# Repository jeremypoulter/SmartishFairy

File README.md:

# SmartishFairy

## Overview
SmartishFairy is a smart controller for inexpensive consumer fairy lights that provides advanced control features at an affordable price. This project allows you to transform ordinary fairy light strings into programmable, dynamic lighting installations with various effects and control options.

### Key Features
- Control up to 12 output channels (6 pairs of lights)
- Support for high voltage input (up to 50V)
- Multiple operating modes for different control schemes
- Compatible with common lighting protocols (WS2812, SPI)
- Based on the powerful RP2040 microcontroller
- Cost-effective solution for home or commercial lighting displays

## Hardware Specifications

### Power and Output
- Input voltage: up to 50V DC
- Output channels: 12 channels total (6 sets, assuming 2 channels per set)
- Driver: 3 × L6226QTR dual channel motor drivers

### Driver Configuration
- Each driver has separate input - jumper available to link input rails
- Output side presents source voltage and ground for independent channels

### Pin Requirements
- 12 output pins (for driving the L6226QTR controllers)
- 8 configuration pins
- 3 SPI pins (possibly 4 if chip select is needed)
- Based on the RP2040 microcontroller

## Operating Modes

### Output Modes (2 bits per driver, 6 bits total)
| Mode | Description |
|------|-------------|
| 0 | Switching - Simple on/off control |
| 1 | TBD (Reserved for future implementation) |
| 2 | Independent high is on - Active high control |
| 3 | Independent low is on - Active low control |

### Input Modes (2 bits)
| Mode | Protocol | Description |
|------|----------|-------------|
| 0 | WS2812 | Neopixel-compatible protocol |
| 1 | SPI | Standard SPI interface |
| 2 | RGB | RGB values converted to brightness (12 virtual RGB lights map to 12 outputs) |
| 3 | Single | Each input channel controls an output (4 virtual RGB elements map to 12 output channels) |

## Installation and Setup

### Hardware Requirements
- RP2040-based board (such as Raspberry Pi Pico)
- 3 × L6226QTR dual channel motor drivers
- Appropriate power supply (rated for your fairy lights, up to 50V)
- Connecting wires/jumpers
- Fairy light strings (compatible with the voltage of your setup)

### Wiring
1. Connect the RP2040 to the L6226QTR drivers according to the pin mapping in the firmware
2. Set configuration jumpers according to your desired operating mode
3. Connect the power supply to the input rails
4. Connect fairy lights to the output channels

For detailed wiring diagrams, refer to the `docs/wiring.md` file in this repository.

## Firmware Setup

### Prerequisites
- C/C++ development environment for RP2040
- Raspberry Pi Pico SDK
- USB cable for programming

### Installation Steps
1. Clone this repository
   ```
   git clone https://github.com/JeremyPoulter/SmartishFairy.git
   ```
2. Configure the firmware based on your setup
3. Compile and flash to the RP2040 board

For detailed firmware instructions, see `docs/firmware.md`.

## Usage Examples

### Basic Control
To control the lights with basic on/off functionality, set the output mode to 0 (switching).

### RGB Control
To use RGB color control:
1. Set the input mode to 2 (RGB)
2. Send RGB color values via the configured input protocol
3. The controller automatically maps these values to brightness levels on the physical outputs

### Independent Channel Control
For direct control of individual channels:
1. Set the input mode to 3 (Single)
2. Control each output channel independently

## Troubleshooting

| Problem | Possible Solution |
|---------|------------------|
| No lights turn on | Check power supply and connections |
| Lights flicker unexpectedly | Verify ground connections and check for EMI sources |
| Cannot program the controller | Ensure USB connection is secure and drivers are installed |

## Resources
- [RP2040 Hardware Design Guide](https://datasheets.raspberrypi.com/rp2040/hardware-design-with-rp2040.pdf)
- [L6226QTR Datasheet](https://www.st.com/resource/en/datasheet/l6226q.pdf)

## Contributing
Contributions to the SmartishFairy project are welcome! Please feel free to submit pull requests or open issues for bugs, questions, or feature requests.

## License
This project is licensed under the MIT License - see the LICENSE file for details.

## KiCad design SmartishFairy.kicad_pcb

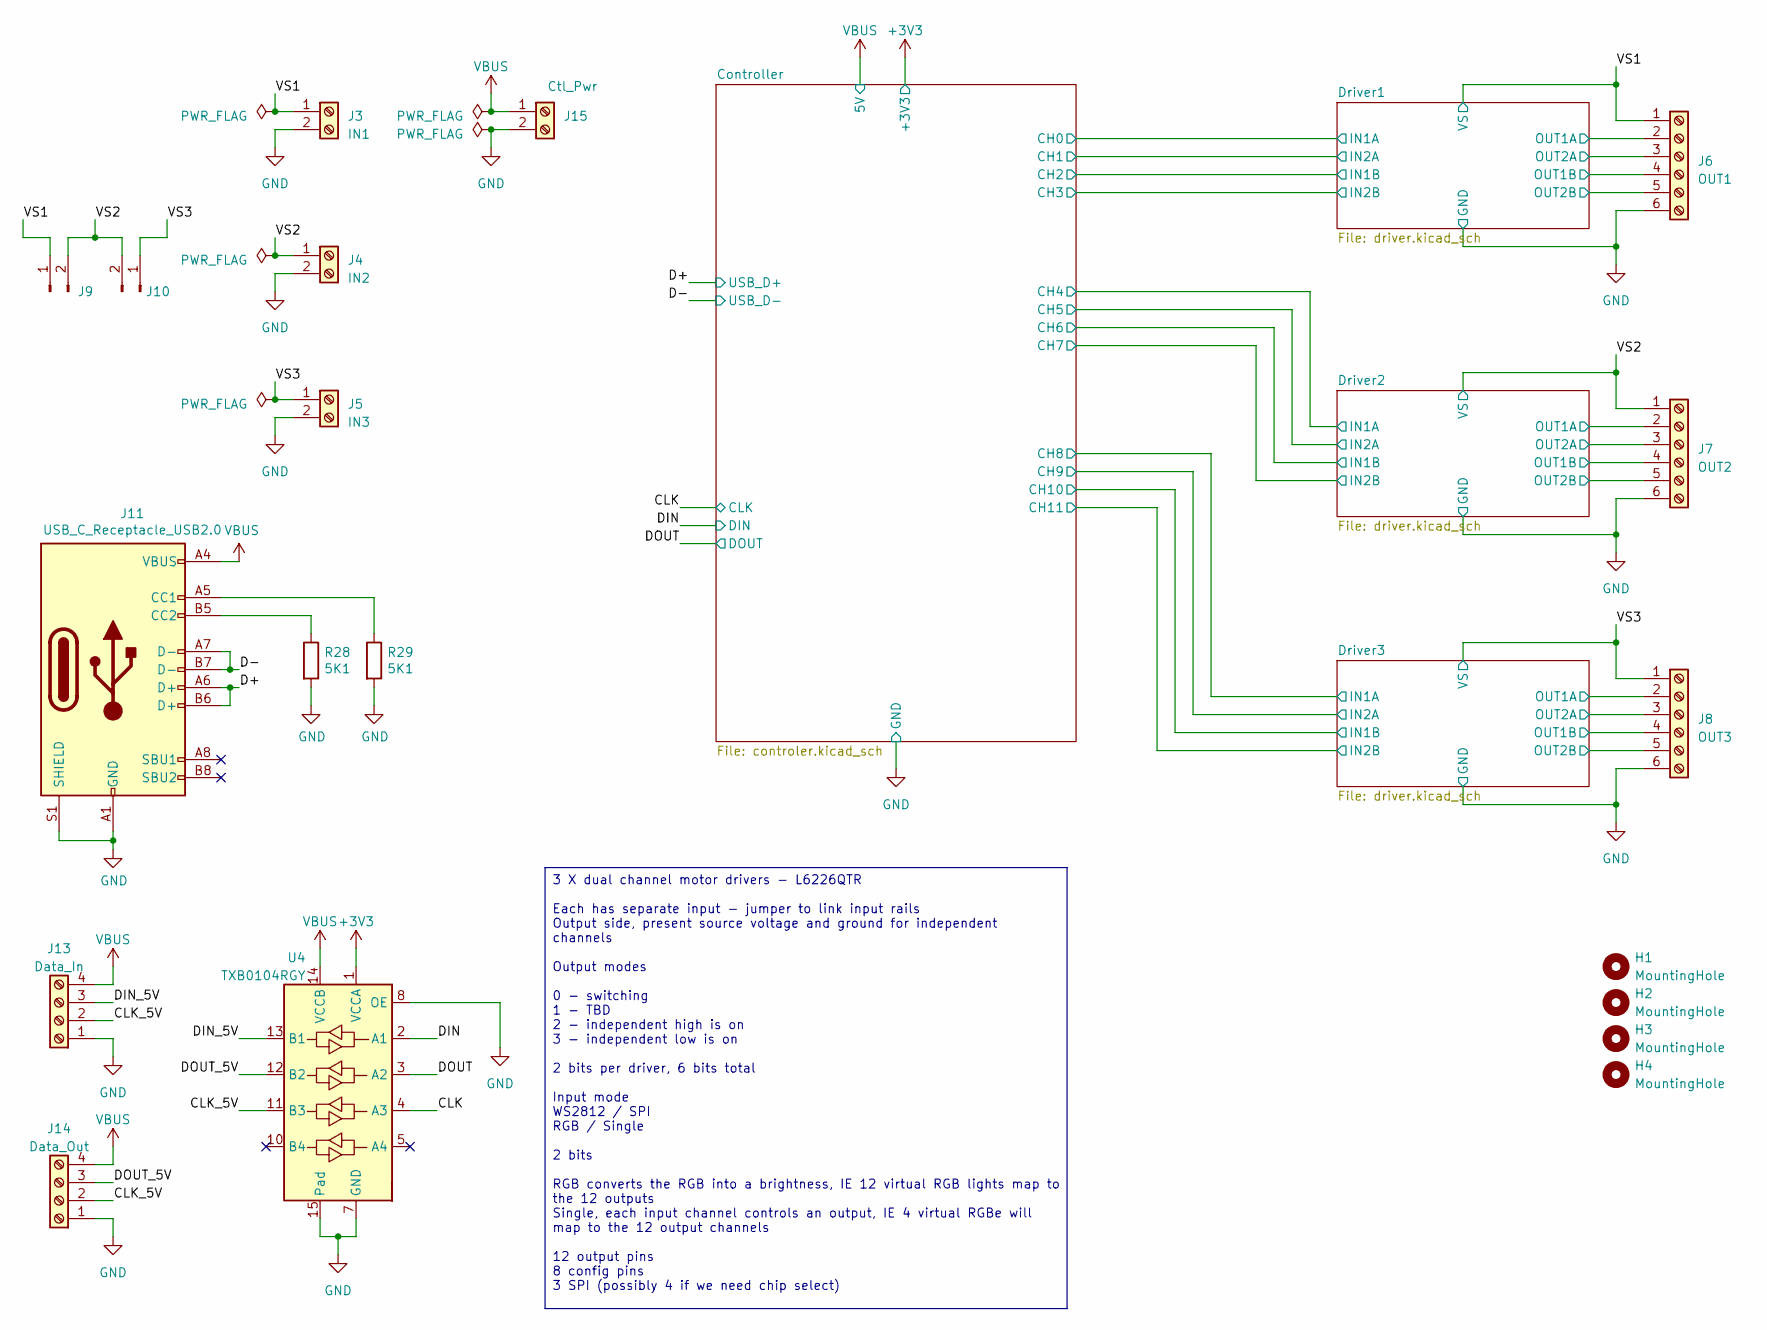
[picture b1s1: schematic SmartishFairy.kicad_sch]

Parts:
H1, H2, H3, H4: MountingHole; MountingHole_3mm
J3: IN1; TerminalBlock_TE_282834-2_1x02_P2.54mm_Horizontal
J4: IN2; TerminalBlock_TE_282834-2_1x02_P2.54mm_Horizontal
J5: IN3; TerminalBlock_TE_282834-2_1x02_P2.54mm_Horizontal
J6: OUT1; TerminalBlock_TE_282834-6_1x06_P2.54mm_Horizontal
J7: OUT2; TerminalBlock_TE_282834-6_1x06_P2.54mm_Horizontal
J8: OUT3; TerminalBlock_TE_282834-6_1x06_P2.54mm_Horizontal
J9, J10: Conn_01x02_Pin; PinHeader_1x02_P2.54mm_Vertical
J11: USB_C_Receptacle_USB2.0; USB_C_Receptacle_HRO_TYPE-C-31-M-12; LCSC C165948
J13: Data_In; TerminalBlock_TE_282834-4_1x04_P2.54mm_Horizontal
J14: Data_Out; TerminalBlock_TE_282834-4_1x04_P2.54mm_Horizontal
J15: Ctl_Pwr; TerminalBlock_TE_282834-2_1x02_P2.54mm_Horizontal
R28, R29: 5K1; R_0402_1005Metric
U4: TXB0104RGY; Texas_S-PVQFN-N14

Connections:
+3V3: U4.1 (VCCA); also elsewhere on the board
/CLK: U4.4 (A3); also elsewhere on the board
/CLK_5V: J13.2, J14.2, U4.11 (B3)
/D+: J11.A6 (D+), J11.B6 (D+); also elsewhere on the board
/D-: J11.A7 (D-), J11.B7 (D-); also elsewhere on the board
/DIN: U4.2 (A1); also elsewhere on the board
/DIN_5V: J13.3, U4.13 (B1)
/DOUT: U4.3 (A2); also elsewhere on the board
/DOUT_5V: J14.3, U4.12 (B2)
/Driver1/OUT1A: J6.2; also elsewhere on the board
/Driver1/OUT1B: J6.4; also elsewhere on the board
/Driver1/OUT2A: J6.3; also elsewhere on the board
/Driver1/OUT2B: J6.5; also elsewhere on the board
/Driver2/OUT1A: J7.2; also elsewhere on the board
/Driver2/OUT1B: J7.4; also elsewhere on the board
/Driver2/OUT2A: J7.3; also elsewhere on the board
/Driver2/OUT2B: J7.5; also elsewhere on the board
/Driver3/OUT1A: J8.2; also elsewhere on the board
/Driver3/OUT1B: J8.4; also elsewhere on the board
/Driver3/OUT2A: J8.3; also elsewhere on the board
/Driver3/OUT2B: J8.5; also elsewhere on the board
/VS1: J3.1, J6.1, J9.1; also elsewhere on the board
/VS2: J4.1, J7.1, J9.2, J10.2; also elsewhere on the board
/VS3: J5.1, J8.1, J10.1; also elsewhere on the board
GND: J3.2, J4.2, J5.2, J6.6, J7.6, J8.6, J11.A1 (GND), J11.A12 (GND), J11.B1 (GND), J11.B12 (GND), J11.S1 (SHIELD), J13.1, J14.1, J15.2, R28.2, R29.2, U4.7 (GND), U4.8 (OE), U4.15 (Pad); also elsewhere on the board
unnamed: J11.A5 (CC1), R29.1
unnamed: J11.B5 (CC2), R28.1
VBUS: J11.A4 (VBUS), J11.A9 (VBUS), J11.B4 (VBUS), J11.B9 (VBUS), J13.4, J14.4, J15.1, U4.14 (VCCB); also elsewhere on the board

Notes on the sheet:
3 X dual channel motor drivers - L6226QTR Each has separate input - jumper to link input rails Output side, present source voltage and ground for independent channels Output modes 0 - switching 1 - TBD 2 - independent high is on 3 - independent low is on 2 bits per driver, 6 bits total Input mode W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

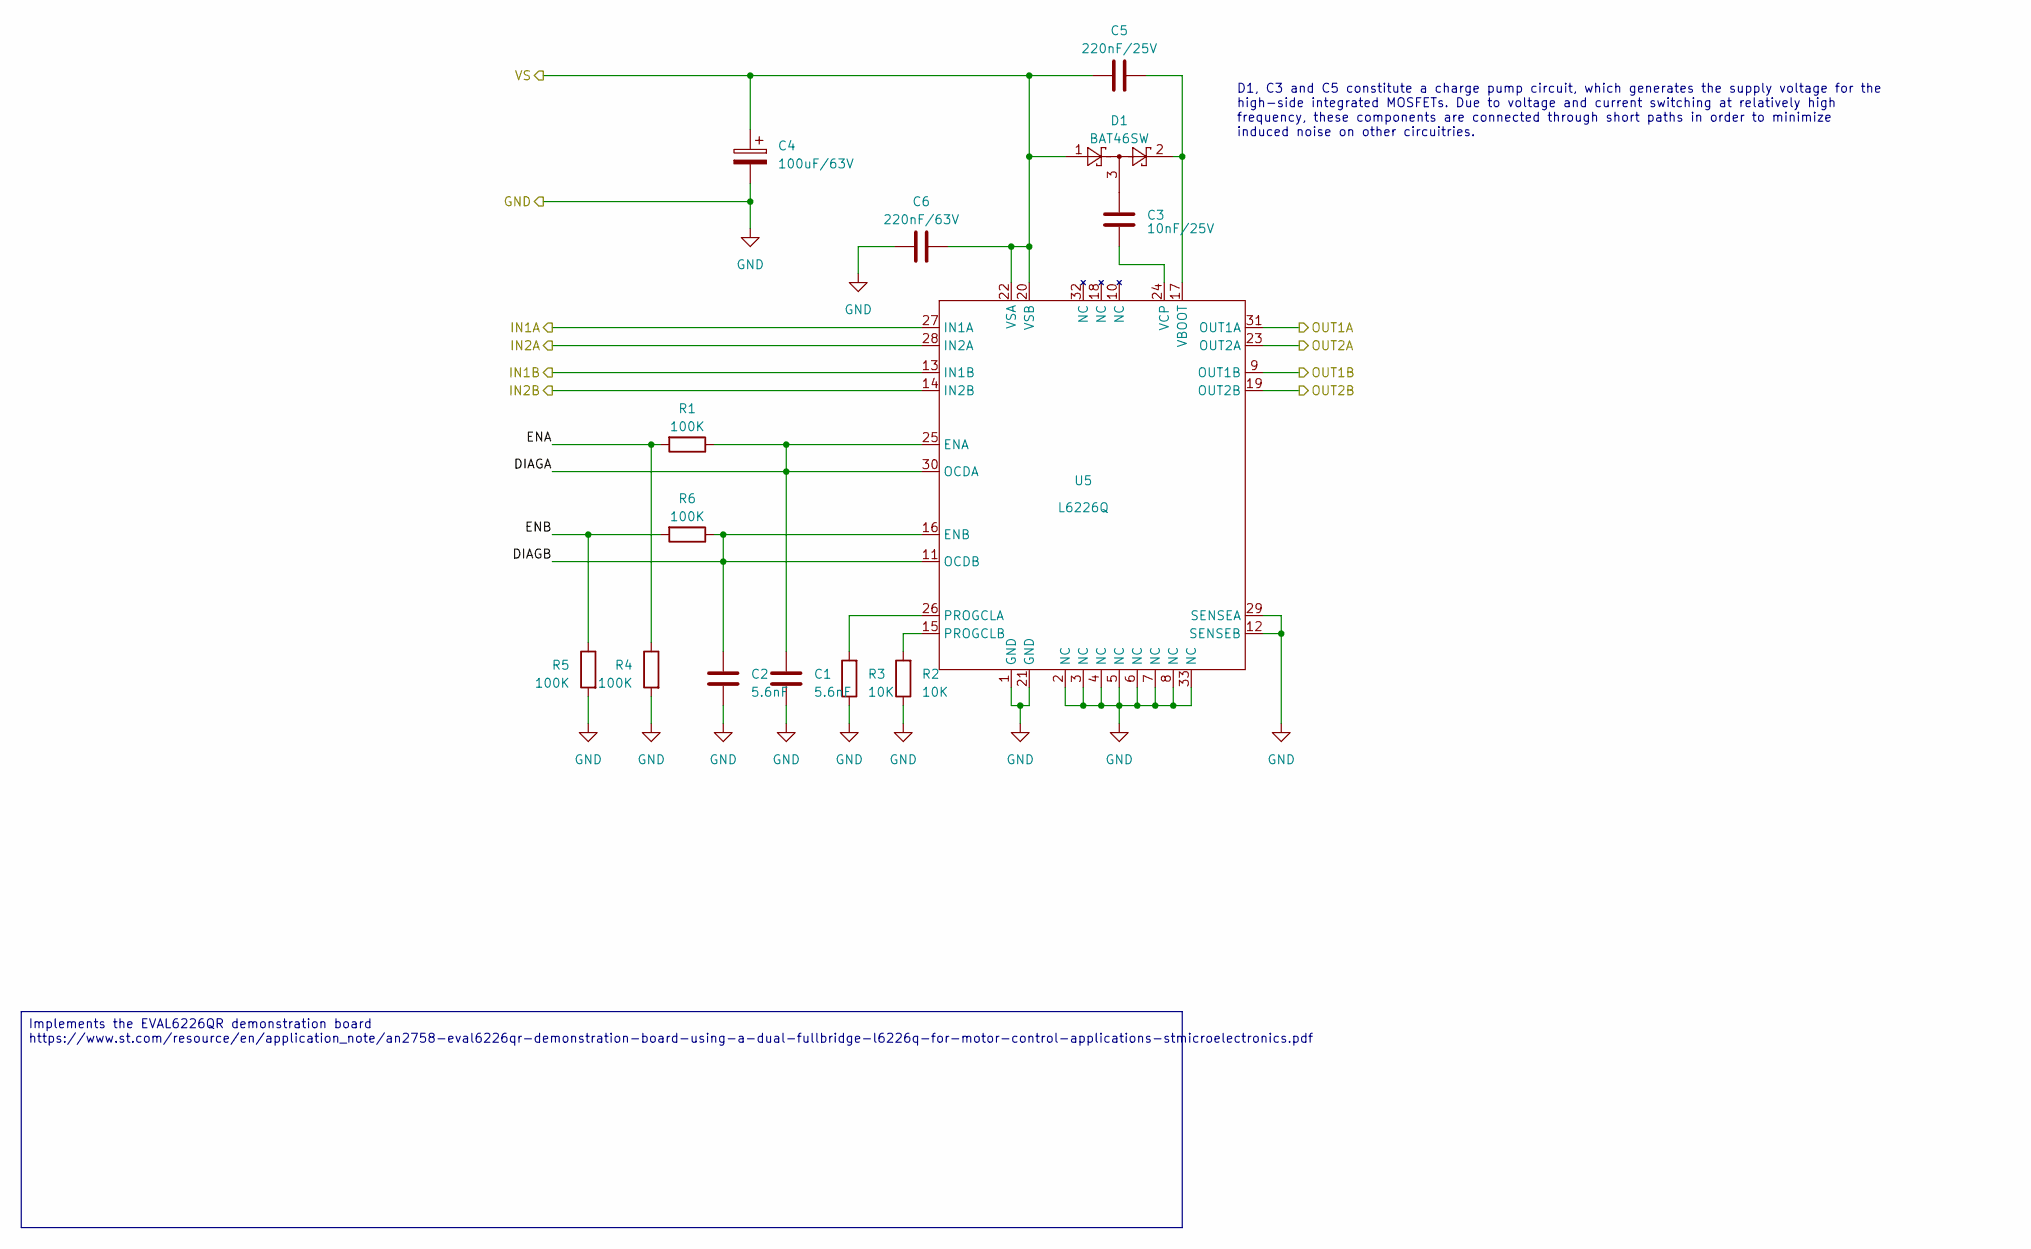
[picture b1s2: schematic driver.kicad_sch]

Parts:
C1, C2: 5.6nF; C_0603_1608Metric
C3: 10nF/25V; C_0603_1608Metric
C4: 100uF/63V; CP_Elec_5x4.4
C5: 220nF/25V; C_0603_1608Metric
C6: 220nF/63V; C_0603_1608Metric
D1: BAT46SW; SOT-23
R1, R4, R5, R6: 100K; R_0603_1608Metric
R2, R3: 10K; R_0603_1608Metric
U5: L6226Q; QFN-32-1EP_5x5mm_P0.5mm_EP3.1x3.1mm

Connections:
/Controller/CH0: U5.27 (IN1A); also elsewhere on the board
/Controller/CH1: U5.28 (IN2A); also elsewhere on the board
/Controller/CH2: U5.13 (IN1B); also elsewhere on the board
/Controller/CH3: U5.14 (IN2B); also elsewhere on the board
/Driver1/DIAGA: C1.1, R1.1, U5.25 (ENA), U5.30 (OCDA)
/Driver1/DIAGB: C2.1, R6.1, U5.11 (OCDB), U5.16 (ENB)
/Driver1/ENA: R1.2, R4.1
/Driver1/ENB: R5.1, R6.2
/Driver1/OUT1A: U5.31 (OUT1A); also elsewhere on the board
/Driver1/OUT1B: U5.9 (OUT1B); also elsewhere on the board
/Driver1/OUT2A: U5.23 (OUT2A); also elsewhere on the board
/Driver1/OUT2B: U5.19 (OUT2B); also elsewhere on the board
/VS1: C4.1, C5.1, C6.2, D1.1, U5.20 (VSB), U5.22 (VSA); also elsewhere on the board
GND: C1.2, C2.2, C4.2, C6.1, R2.1, R3.1, R4.2, R5.2, U5.1 (GND), U5.2 (NC), U5.3 (NC), U5.4 (NC), U5.5 (NC), U5.6 (NC), U5.7 (NC), U5.8 (NC), U5.12 (SENSEB), U5.21 (GND), U5.29 (SENSEA), U5.33 (NC); also elsewhere on the board
unnamed: C3.1, D1.3
unnamed: R3.2, U5.26 (PROGCLA)
unnamed: R2.2, U5.15 (PROGCLB)
unnamed: C5.2, D1.2, U5.17 (VBOOT)
unnamed: C3.2, U5.24 (VCP)

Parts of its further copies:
C7, C9, C13, C15: 5.6nF; C_0603_1608Metric
C8, C14: 100uF/63V; CP_Elec_5x4.4
C10, C16: 220nF/63V; C_0603_1608Metric
C11, C17: 220nF/25V; C_0603_1608Metric
C12, C18: 10nF/25V; C_0603_1608Metric
D2, D3: BAT46SW; SOT-23
R7, R8, R9, R10, R13, R14, R15, R16: 100K; R_0603_1608Metric
R11, R12, R17, R18: 10K; R_0603_1608Metric
U6, U7: L6226Q; QFN-32-1EP_5x5mm_P0.5mm_EP3.1x3.1mm

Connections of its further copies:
/Controller/CH4: U6.27 (IN1A); also elsewhere on the board
/Controller/CH5: U6.28 (IN2A); also elsewhere on the board
/Controller/CH6: U6.13 (IN1B); also elsewhere on the board
/Controller/CH7: U6.14 (IN2B); also elsewhere on the board
/Controller/CH8: U7.27 (IN1A); also elsewhere on the board
/Controller/CH9: U7.28 (IN2A); also elsewhere on the board
/Controller/CH10: U7.13 (IN1B); also elsewhere on the board
/Controller/CH11: U7.14 (IN2B); also elsewhere on the board
/Driver2/DIAGA: C9.1, R9.1, U6.25 (ENA), U6.30 (OCDA)
/Driver2/DIAGB: C7.1, R10.1, U6.11 (OCDB), U6.16 (ENB)
/Driver2/ENA: R8.1, R9.2
/Driver2/ENB: R7.1, R10.2
/Driver2/OUT1A: U6.31 (OUT1A); also elsewhere on the board
/Driver2/OUT1B: U6.9 (OUT1B); also elsewhere on the board
/Driver2/OUT2A: U6.23 (OUT2A); also elsewhere on the board
/Driver2/OUT2B: U6.19 (OUT2B); also elsewhere on the board
/Driver3/DIAGA: C15.1, R15.1, U7.25 (ENA), U7.30 (OCDA)
/Driver3/DIAGB: C13.1, R16.1, U7.11 (OCDB), U7.16 (ENB)
/Driver3/ENA: R14.1, R15.2
/Driver3/ENB: R13.1, R16.2
/Driver3/OUT1A: U7.31 (OUT1A); also elsewhere on the board
/Driver3/OUT1B: U7.9 (OUT1B); also elsewhere on the board
/Driver3/OUT2A: U7.23 (OUT2A); also elsewhere on the board
/Driver3/OUT2B: U7.19 (OUT2B); also elsewhere on the board
/VS2: C8.1, C10.2, C11.1, D2.1, U6.20 (VSB), U6.22 (VSA); also elsewhere on the board
/VS3: C14.1, C16.2, C17.1, D3.1, U7.20 (VSB), U7.22 (VSA); also elsewhere on the board
GND: C7.2, C8.2, C9.2, C10.1, C13.2, C14.2, C15.2, C16.1, R7.2, R8.2, R11.1, R12.1, R13.2, R14.2, R17.1, R18.1, U6.1 (GND), U6.2 (NC), U6.3 (NC), U6.4 (NC), U6.5 (NC), U6.6 (NC), U6.7 (NC), U6.8 (NC), U6.12 (SENSEB), U6.21 (GND), U6.29 (SENSEA), U6.33 (NC), U7.1 (GND), U7.2 (NC), U7.3 (NC), U7.4 (NC), U7.5 (NC), U7.6 (NC), U7.7 (NC), U7.8 (NC), U7.12 (SENSEB), U7.21 (GND), U7.29 (SENSEA), U7.33 (NC); also elsewhere on the board
unnamed: C12.1, D2.3
unnamed: C18.1, D3.3
unnamed: R11.2, U6.26 (PROGCLA)
unnamed: R12.2, U6.15 (PROGCLB)
unnamed: C11.2, D2.2, U6.17 (VBOOT)
unnamed: C12.2, U6.24 (VCP)
unnamed: R17.2, U7.26 (PROGCLA)
unnamed: R18.2, U7.15 (PROGCLB)
unnamed: C17.2, D3.2, U7.17 (VBOOT)
unnamed: C18.2, U7.24 (VCP)

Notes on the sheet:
D1, C3 and C5 constitute a charge pump circuit, which generates the supply voltage for the high-side integrated MOSFETs. Due to voltage and current switching at relatively high frequency, these components are connected through short paths in order to minimize induced noise on other circuitries.
Implements the EVAL6226QR demonstration board https://www.st.com/resource/en/application_note/an2758-eval6226qr-demonstration-board-using-a-dual-fullbridge-l6226q-for-motor-control-applications-stmicroelectronics.pdf

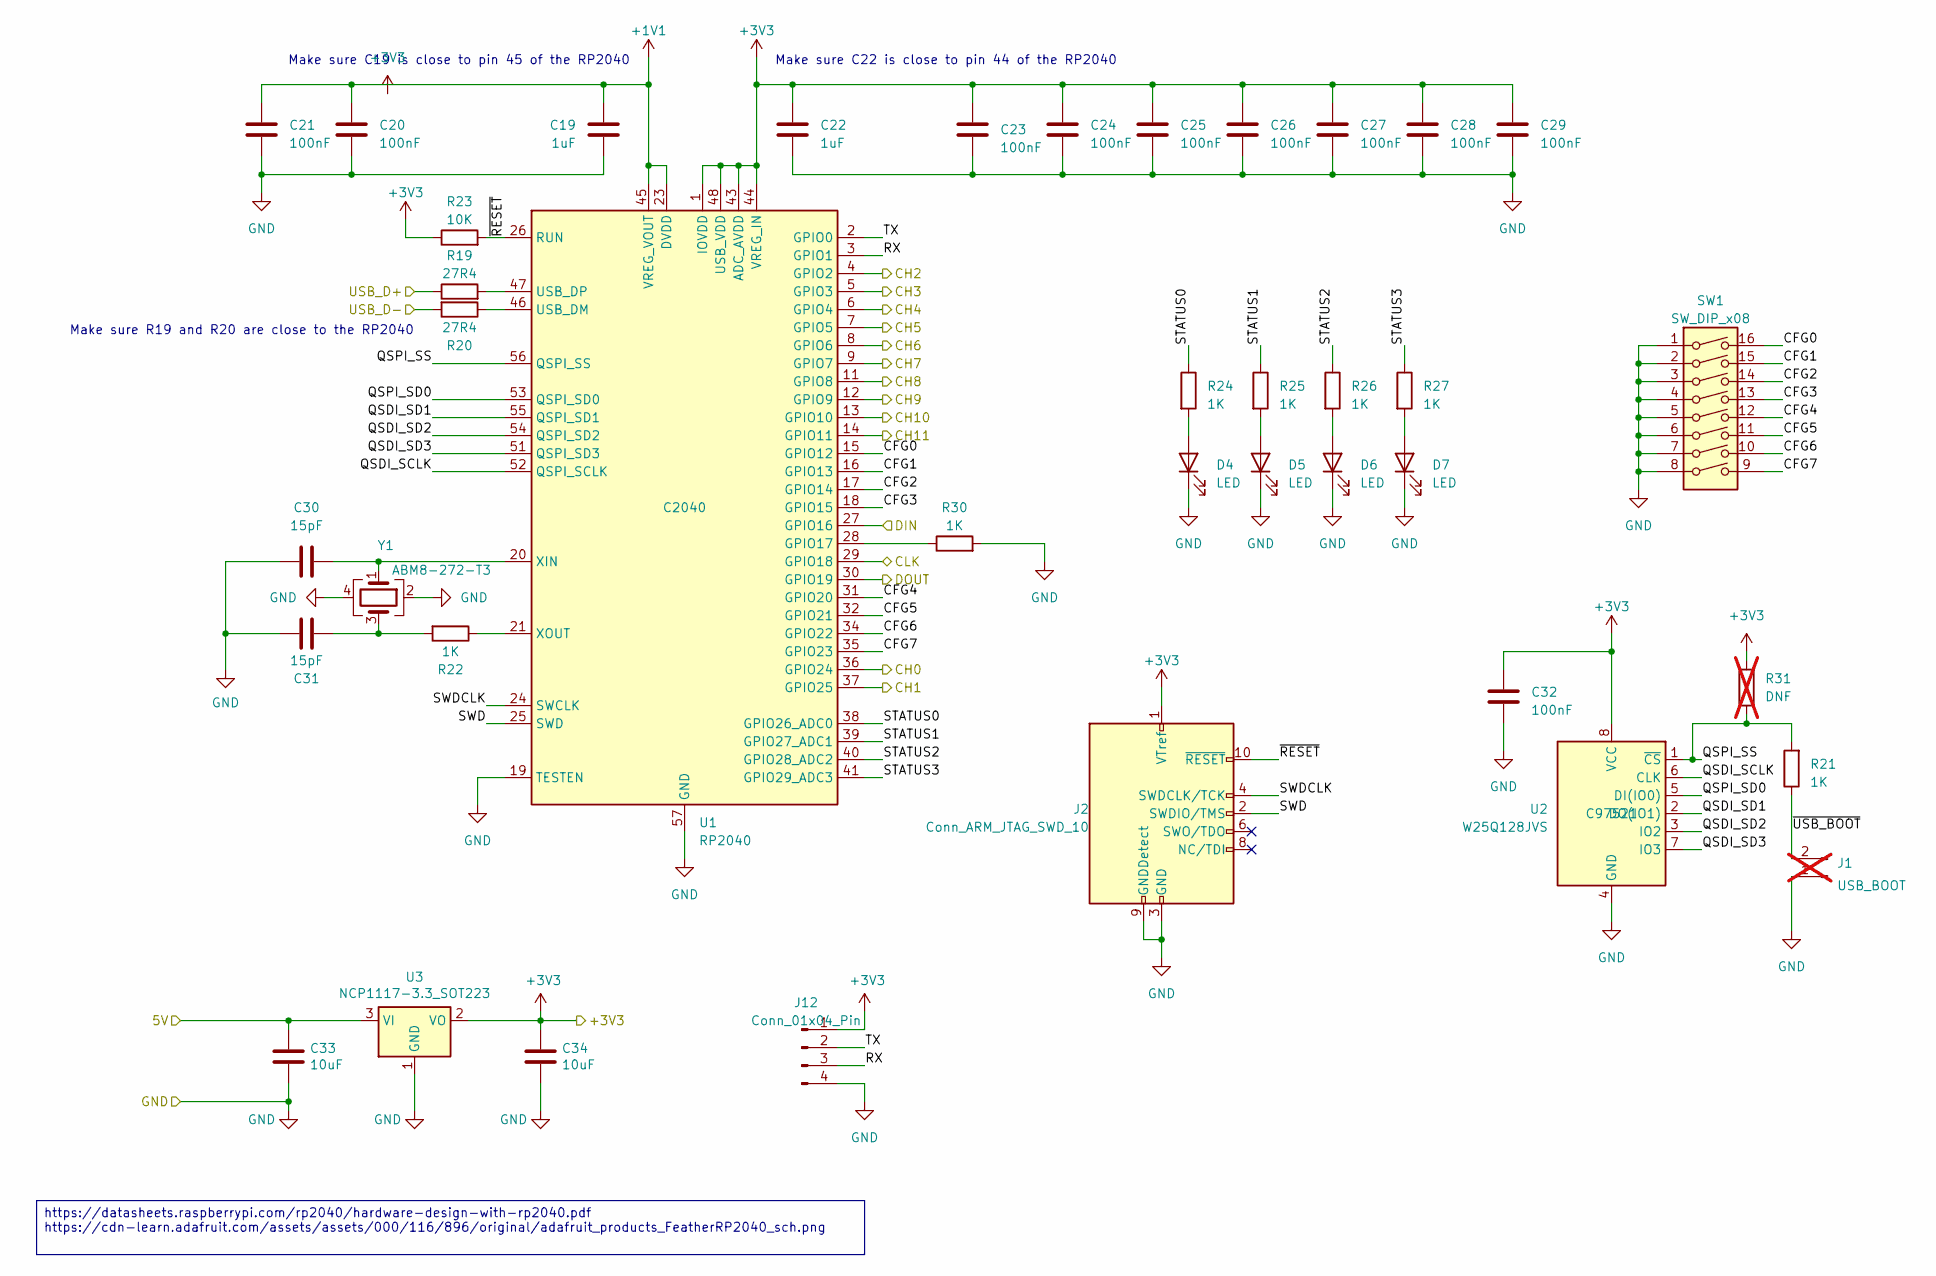
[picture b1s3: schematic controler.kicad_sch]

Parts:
C19, C22: 1uF; C_0402_1005Metric
C20, C21, C23, C24, C25, C26, C27, C28, C29, C32: 100nF; C_0402_1005Metric
C30, C31: 15pF; C_0402_1005Metric
C33, C34: 10uF; C_0603_1608Metric
D4, D5, D6, D7: LED; LED_0805_2012Metric
J1: USB_BOOT; PinHeader_1x02_P2.54mm_Vertical; not fitted
J2: Conn_ARM_JTAG_SWD_10; PinHeader_2x05_P1.27mm_Vertical_SMD
J12: Conn_01x04_Pin; PinHeader_1x04_P2.54mm_Vertical
R19, R20: 27R4; R_0402_1005Metric
R21, R22, R24, R25, R26, R27, R30: 1K; R_0402_1005Metric
R23: 10K; R_0402_1005Metric
R31: DNF; R_0402_1005Metric; not fitted
SW1: SW_DIP_x08; SW_DIP_SPSTx08_Slide_9.78x22.5mm_W7.62mm_P2.54mm
U1: RP2040; QFN-56-1EP_7x7mm_P0.4mm_EP3.2x3.2mm; LCSC C2040
U2: W25Q128JVS; SOIC-8_5.23x5.23mm_P1.27mm; LCSC C97521
U3: NCP1117-3.3_SOT223; SOT-223-3_TabPin2
Y1: ABM8-272-T3; Crystal_SMD_3225-4Pin_3.2x2.5mm; LCSC C20625731

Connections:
+1V1: C19.1, C20.1, C21.1, U1.23 (DVDD), U1.45 (VREG_VOUT), U1.50 (DVDD)
+3V3: C22.1, C23.1, C24.1, C25.1, C26.1, C27.1, C28.1, C29.1, C32.1, C34.1, J2.1 (VTref), J12.1, R23.1, R31.2, U1.1 (IOVDD), U1.10 (IOVDD), U1.22 (IOVDD), U1.33 (IOVDD), U1.42 (IOVDD), U1.43 (ADC_AVDD), U1.44 (VREG_IN), U1.48 (USB_VDD), U1.49 (IOVDD), U2.8 (VCC), U3.2 (VO); also elsewhere on the board
/CLK: U1.29 (GPIO18); also elsewhere on the board
/Controller/CFG0: SW1.16, U1.15 (GPIO12)
/Controller/CFG1: SW1.15, U1.16 (GPIO13)
/Controller/CFG2: SW1.14, U1.17 (GPIO14)
/Controller/CFG3: SW1.13, U1.18 (GPIO15)
/Controller/CFG4: SW1.12, U1.31 (GPIO20)
/Controller/CFG5: SW1.11, U1.32 (GPIO21)
/Controller/CFG6: SW1.10, U1.34 (GPIO22)
/Controller/CFG7: SW1.9, U1.35 (GPIO23)
/Controller/CH0: U1.36 (GPIO24); also elsewhere on the board
/Controller/CH1: U1.37 (GPIO25); also elsewhere on the board
/Controller/CH2: U1.4 (GPIO2); also elsewhere on the board
/Controller/CH3: U1.5 (GPIO3); also elsewhere on the board
/Controller/CH4: U1.6 (GPIO4); also elsewhere on the board
/Controller/CH5: U1.7 (GPIO5); also elsewhere on the board
/Controller/CH6: U1.8 (GPIO6); also elsewhere on the board
/Controller/CH7: U1.9 (GPIO7); also elsewhere on the board
/Controller/CH8: U1.11 (GPIO8); also elsewhere on the board
/Controller/CH9: U1.12 (GPIO9); also elsewhere on the board
/Controller/CH10: U1.13 (GPIO10); also elsewhere on the board
/Controller/CH11: U1.14 (GPIO11); also elsewhere on the board
/Controller/QSDI_SCLK: U1.52 (QSPI_SCLK), U2.6 (CLK)
/Controller/QSDI_SD1: U1.55 (QSPI_SD1), U2.2 (DO(IO1))
/Controller/QSDI_SD2: U1.54 (QSPI_SD2), U2.3 (IO2)
/Controller/QSDI_SD3: U1.51 (QSPI_SD3), U2.7 (IO3)
/Controller/QSPI_SD0: U1.53 (QSPI_SD0), U2.5 (DI(IO0))
/Controller/QSPI_SS: R21.2, R31.1, U1.56 (QSPI_SS), U2.1 (~CS)
/Controller/RX: J12.3, U1.3 (GPIO1)
/Controller/STATUS0: R24.1, U1.38 (GPIO26_ADC0)
/Controller/STATUS1: R25.1, U1.39 (GPIO27_ADC1)
/Controller/STATUS2: R26.1, U1.40 (GPIO28_ADC2)
/Controller/STATUS3: R27.1, U1.41 (GPIO29_ADC3)
/Controller/SWD: J2.2 (SWDIO/TMS), U1.25 (SWD)
/Controller/SWDCLK: J2.4 (SWDCLK/TCK), U1.24 (SWCLK)
/Controller/TX: J12.2, U1.2 (GPIO0)
/Controller/~RESET: J2.10 (~RESET), R23.2, U1.26 (RUN)
/Controller/~USB_BOOT: J1.2, R21.1
/D+: R19.1; also elsewhere on the board
/D-: R20.2; also elsewhere on the board
/DIN: U1.27 (GPIO16); also elsewhere on the board
/DOUT: U1.30 (GPIO19); also elsewhere on the board
GND: C19.2, C20.2, C21.2, C22.2, C23.2, C24.2, C25.2, C26.2, C27.2, C28.2, C29.2, C30.1, C31.2, C32.2, C33.2, C34.2, D4.1 (K), D5.1 (K), D6.1 (K), D7.1 (K), J1.1, J2.3 (GND), J2.5 (GND), J2.9 (GNDDetect), J12.4, R30.2, SW1.1, SW1.2, SW1.3, SW1.4, SW1.5, SW1.6, SW1.7, SW1.8, U1.19 (TESTEN), U1.57 (GND), U2.4 (GND), U3.1 (GND), Y1.2, Y1.4; also elsewhere on the board
unnamed: C31.1, R22.2, Y1.3
unnamed: D4.2 (A), R24.2
unnamed: D5.2 (A), R25.2
unnamed: D6.2 (A), R26.2
unnamed: D7.2 (A), R27.2
unnamed: R30.1, U1.28 (GPIO17)
unnamed: R20.1, U1.46 (USB_DM)
unnamed: R19.2, U1.47 (USB_DP)
unnamed: C30.2, U1.20 (XIN), Y1.1
unnamed: R22.1, U1.21 (XOUT)
VBUS: C33.1, U3.3 (VI); also elsewhere on the board

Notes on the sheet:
Make sure C22 is close to pin 44 of the RP2040
Make sure C19 is close to pin 45 of the RP2040
Make sure R19 and R20 are close to the RP2040
https://datasheets.raspberrypi.com/rp2040/hardware-design-with-rp2040.pdf https://cdn-learn.adafruit.com/assets/assets/000/116/896/original/adafruit_products_FeatherRP2040_sch.png

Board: 2 copper layers, 100 parts (0 on the bottom side), 102 nets, no tracks yet.

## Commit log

2023-03-19 ECR fixes
2023-03-19 Docs
2023-03-19 Ignore temp/generated KiCAD
2023-03-19 Remove old file
2023-03-19 More ECR fixes
2023-03-19 Initial PCB layout
2025-01-10 Layout WIP
2025-03-20 Convert to KiCAD v9 and basic sort out of components
2025-04-09 Additional layout
2025-04-09 Added notes about features/control
2025-04-10 Added optional pull up resistor for flash chip
2025-04-10 Fleshed out the README a bit
2025-04-10 Added a few JLC part number
2025-04-10 More updates
    Placed more components
    Updated 3D models
